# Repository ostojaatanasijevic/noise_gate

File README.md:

# TPI pedals - BMF

## Schematic

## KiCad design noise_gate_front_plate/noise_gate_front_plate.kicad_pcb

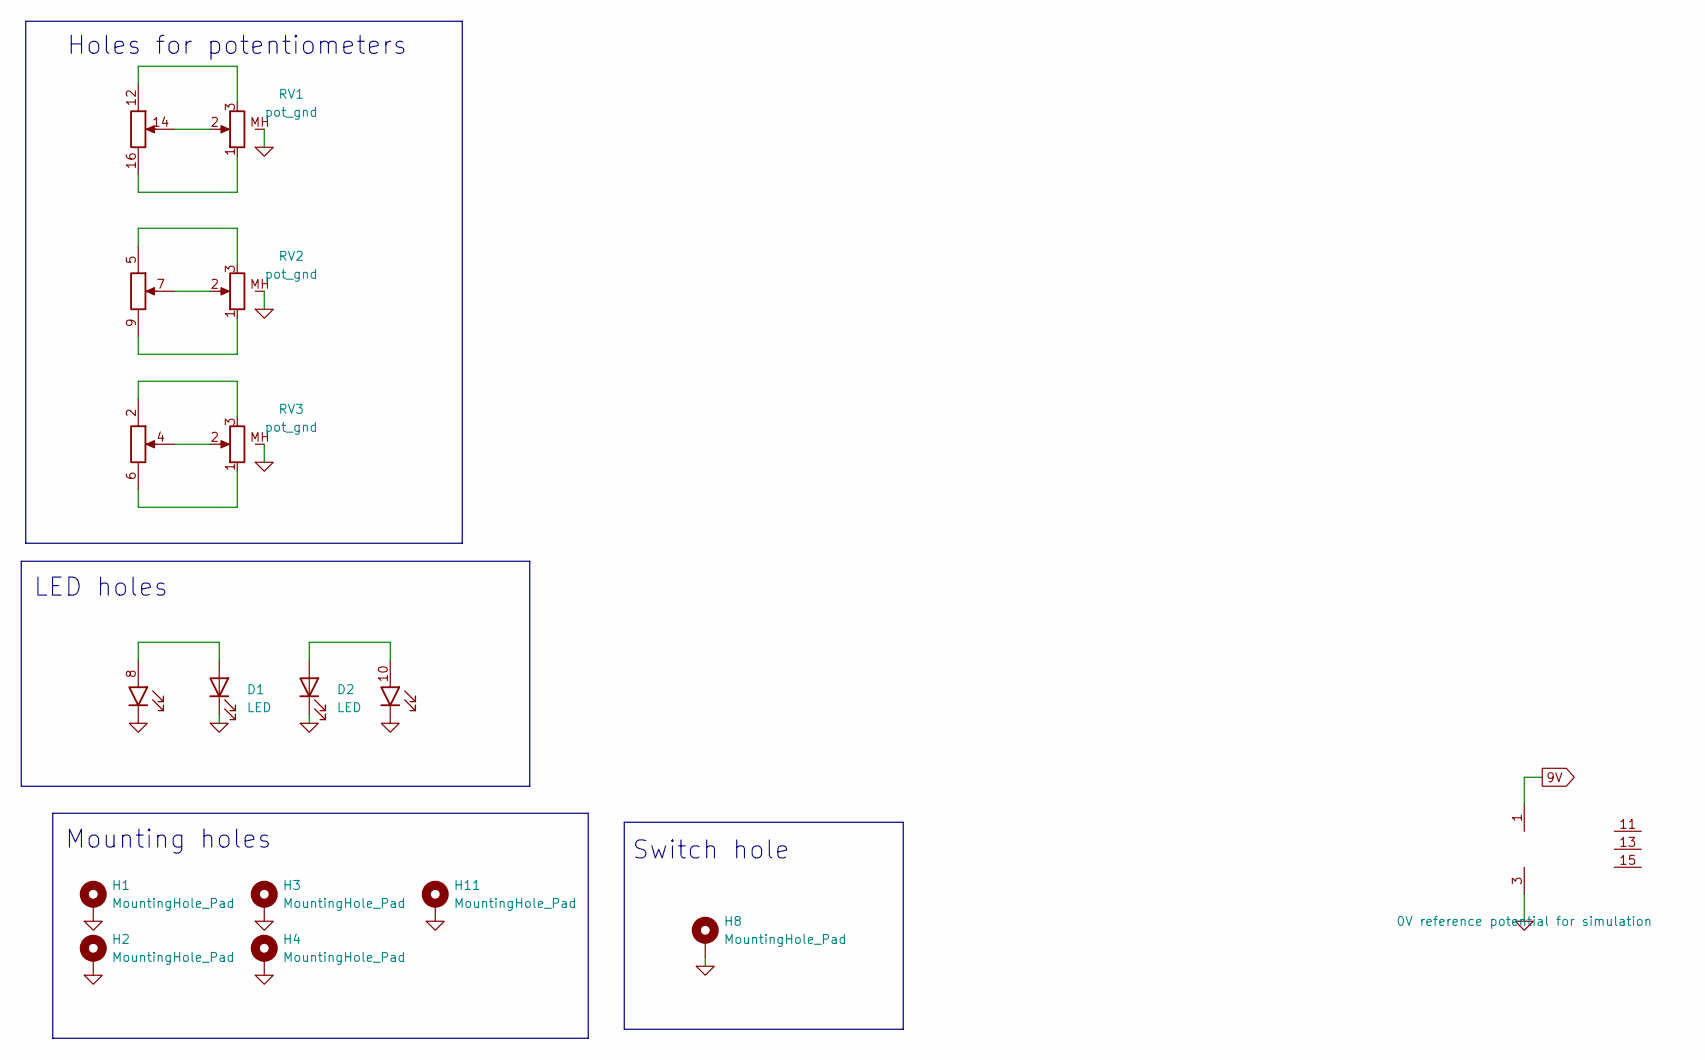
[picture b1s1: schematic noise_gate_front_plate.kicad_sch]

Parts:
D1: LED; red_led
D2: LED; green_led
H1, H2, H3, H4, H11: MountingHole_Pad; MountingHole_3.2mm_M3_DIN965_Pad_TopBottom
H8: MountingHole_Pad; plated_switch_hole
J1: top_panel_connector; IDC-Header_2x08_faux_SMD
RV1, RV2, RV3: pot_gnd; top_plate_pot

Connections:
0: D1.1 (K), D2.1 (K), H1.1, H2.1, H3.1, H4.1, H8.1, H11.1, J1.3 (GND), RV1.MH (2), RV2.MH (2), RV3.MH (2)
9V: J1.1 (VCC)
unnamed: D1.2 (A), J1.8
unnamed: D2.2 (A), J1.10
unnamed: J1.2, RV3.3
unnamed: J1.4, RV3.2
unnamed: J1.6, RV3.1
unnamed: J1.5, RV2.3
unnamed: J1.7, RV2.2
unnamed: J1.9, RV2.1
unnamed: J1.12, RV1.3
unnamed: J1.14, RV1.2
unnamed: J1.16, RV1.1

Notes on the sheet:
Mounting holes
Switch hole
LED holes
Holes for potentiometers

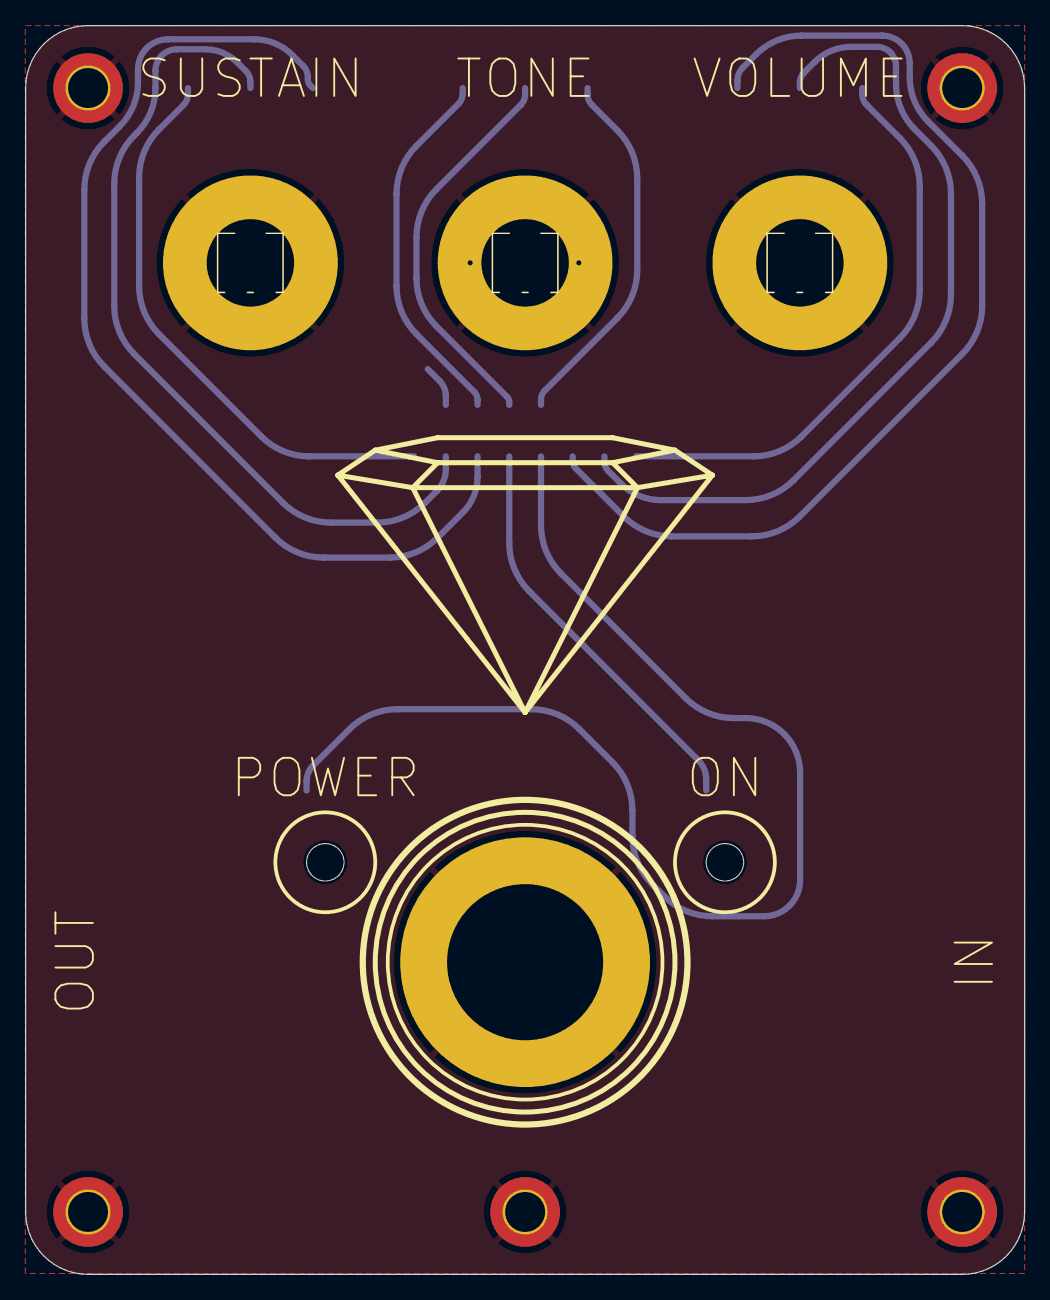
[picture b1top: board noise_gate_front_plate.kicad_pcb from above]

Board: 2 copper layers, 80.0 x 100.0 mm, 12 parts (1 on the bottom side), 12 nets.

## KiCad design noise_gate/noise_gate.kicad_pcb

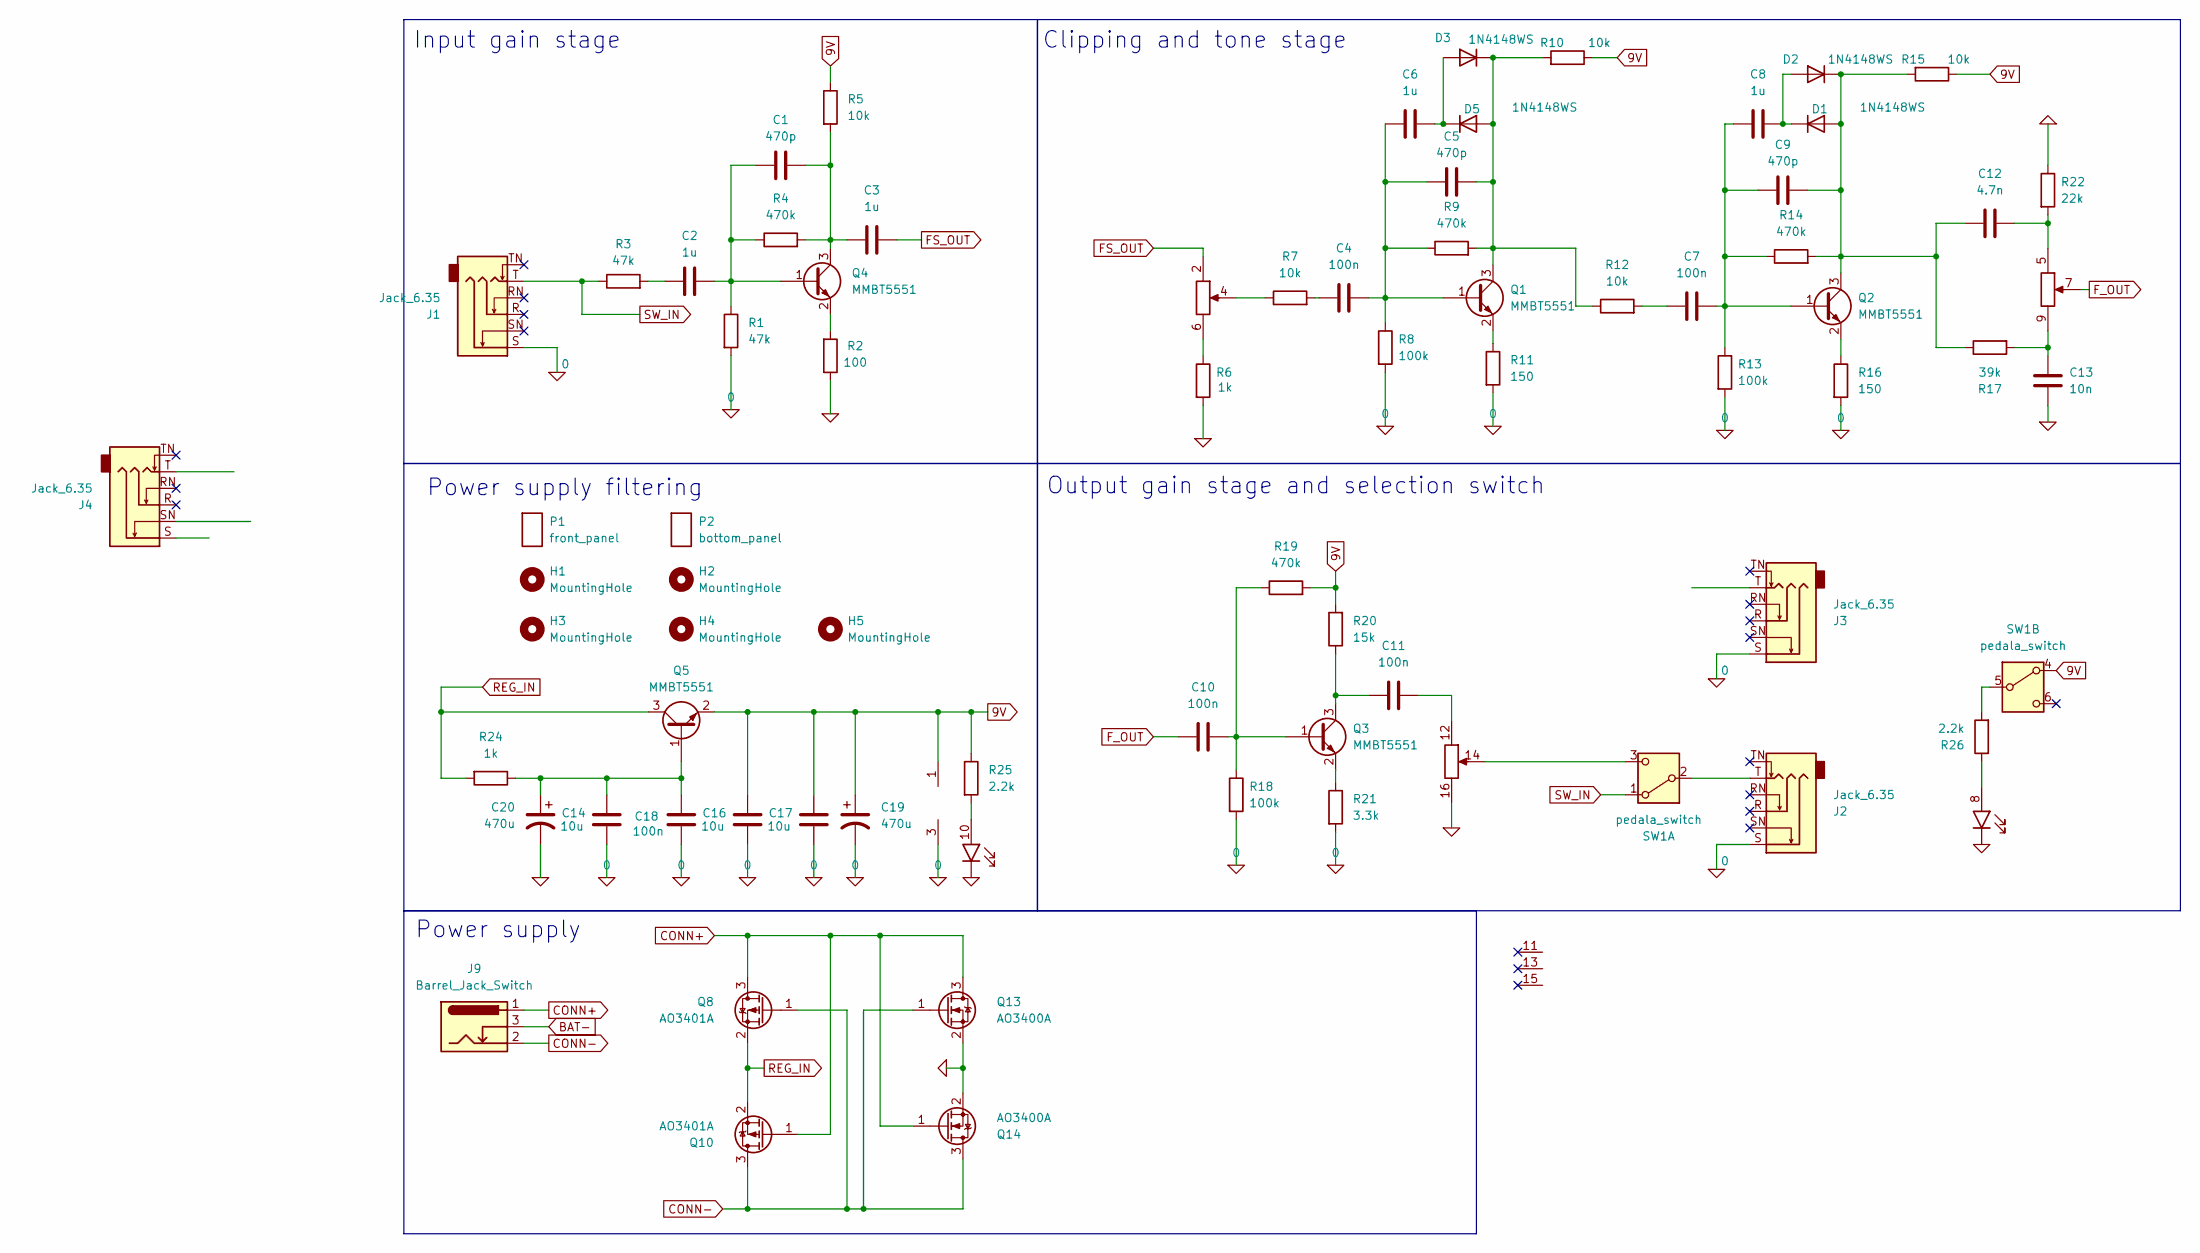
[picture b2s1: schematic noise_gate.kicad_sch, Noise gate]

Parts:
C1, C5, C9: 470p; C_0603_1608Metric_Pad1.08x0.95mm_HandSolder; LCSC C1620
C2, C3, C6, C8: 1u; C_0603_1608Metric_Pad1.08x0.95mm_HandSolder; LCSC C15849
C4, C7, C10, C11, C18: 100n; C_0603_1608Metric_Pad1.08x0.95mm_HandSolder; LCSC C14663
C12: 4.7n; C_0603_1608Metric_Pad1.08x0.95mm_HandSolder; LCSC C53987
C13: 10n; C_0603_1608Metric_Pad1.08x0.95mm_HandSolder; LCSC C57112
C14, C16, C17: 10u; C_0603_1608Metric_Pad1.08x0.95mm_HandSolder; LCSC C96446
C19, C20: 470u; CP_Radial_D8.0mm_P3.50mm
D1, D2, D3, D5: 1N4148WS; D_SOD-323; LCSC C2128
H1, H2, H3, H4, H5: MountingHole; M3_hole_with_spacer
J1, J2, J3, J4: Jack_6.35; Jack_6.35mm
J6: top_panel_connector; IDC-Header_2x08_P2.54mm_Vertical
J9: Barrel_Jack_Switch; BarrelJack
P1: front_panel; front_plate
P2: bottom_panel; bottom_plate
Q1, Q2, Q3, Q4, Q5: MMBT5551; SOT-23; LCSC C2145
Q8, Q10: AO3401A; SOT-23; LCSC C15127
Q13, Q14: AO3400A; SOT-23; LCSC C20917
R1, R3: 47k; R_0603_1608Metric_Pad0.98x0.95mm_HandSolder; LCSC C25819
R2: 100; R_0603_1608Metric_Pad0.98x0.95mm_HandSolder; LCSC C22775
R4, R9, R14, R19: 470k; R_0603_1608Metric_Pad0.98x0.95mm_HandSolder; LCSC C23178
R5, R7, R10, R12, R15: 10k; R_0603_1608Metric_Pad0.98x0.95mm_HandSolder; LCSC C25804
R6, R24: 1k; R_0603_1608Metric_Pad0.98x0.95mm_HandSolder; LCSC C21190
R8, R13, R18: 100k; R_0603_1608Metric_Pad0.98x0.95mm_HandSolder; LCSC C25803
R11, R16: 150; R_0603_1608Metric_Pad0.98x0.95mm_HandSolder; LCSC C22808
R17: 39k; R_0603_1608Metric_Pad0.98x0.95mm_HandSolder; LCSC C23153
R20: 15k; R_0603_1608Metric_Pad0.98x0.95mm_HandSolder; LCSC C22809
R21: 3.3k; R_0603_1608Metric_Pad0.98x0.95mm_HandSolder; LCSC C22978
R22: 22k; R_0603_1608Metric_Pad0.98x0.95mm_HandSolder; LCSC C31850
R25, R26: 2.2k; R_0603_1608Metric_Pad0.98x0.95mm_HandSolder; LCSC C4190
SW1: pedala_switch; foot_switch_tht_no_pad

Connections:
0: C13.1, C14.2, C16.2, C17.2, C18.1, C19.2, C20.2, J1.S, J2.S, J3.S, J6.3 (GND), J6.16, Q13.2 (S), Q14.2 (S), R1.2, R2.1, R6.2, R8.2, R11.2, R13.2, R16.2, R18.2, R21.2, R22.1
9V: C16.1, C17.1, C19.1, J6.1 (VCC), Q5.2 (E), R5.1, R10.1, R15.1, R19.2, R20.2, R25.1, SW1.4 (A)
BAT-: J9.3
CONN+: J9.1, Q8.3 (D), Q10.1 (G), Q13.3 (D), Q14.1 (G)
CONN-: J9.2, Q8.1 (G), Q10.3 (D), Q13.1 (G), Q14.3 (D)
FS_OUT: C3.2, J6.2
F_OUT: C10.1, J6.7
unnamed: C2.1, R3.2
unnamed: C4.1, R7.2
unnamed: C7.1, R12.2
unnamed: C9.2, C12.1, D1.2 (A), D2.1 (K), Q2.3 (C), R14.2, R15.2, R17.1
unnamed: C8.2, D1.1 (K), D2.2 (A)
unnamed: C6.2, D3.2 (A), D5.1 (K)
unnamed: C5.2, D3.1 (K), D5.2 (A), Q1.3 (C), R9.2, R10.2, R12.1
unnamed: J6.4, R7.1
unnamed: J6.6, R6.1
unnamed: C12.2, J6.5, R22.2
unnamed: C13.2, J6.9, R17.2
unnamed: C11.2, J6.12
unnamed: J6.14, SW1.3 (C)
unnamed: J6.8, R26.1
unnamed: J6.10, R25.2
unnamed: C4.2, C5.1, C6.1, Q1.1 (B), R8.1, R9.1
unnamed: Q1.2 (E), R11.1
unnamed: C7.2, C8.1, C9.1, Q2.1 (B), R13.1, R14.1
unnamed: Q2.2 (E), R16.1
unnamed: C10.2, Q3.1 (B), R18.1, R19.1
unnamed: C11.1, Q3.3 (C), R20.1
unnamed: Q3.2 (E), R21.1
unnamed: C1.1, C2.2, Q4.1 (B), R1.1, R4.1
unnamed: C1.2, C3.1, Q4.3 (C), R4.2, R5.2
unnamed: Q4.2 (E), R2.2
unnamed: C14.1, C18.2, C20.1, Q5.1 (B), R24.1
unnamed: J2.T, SW1.2 (B)
unnamed: R26.2, SW1.5 (B)
REG_IN: Q5.3 (C), Q8.2 (S), Q10.2 (S), R24.2
SW_IN: J1.T, R3.1, SW1.1 (A)

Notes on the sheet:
Power supply filtering
Input gain stage
Output gain stage and selection switch
Clipping and tone stage
Power supply

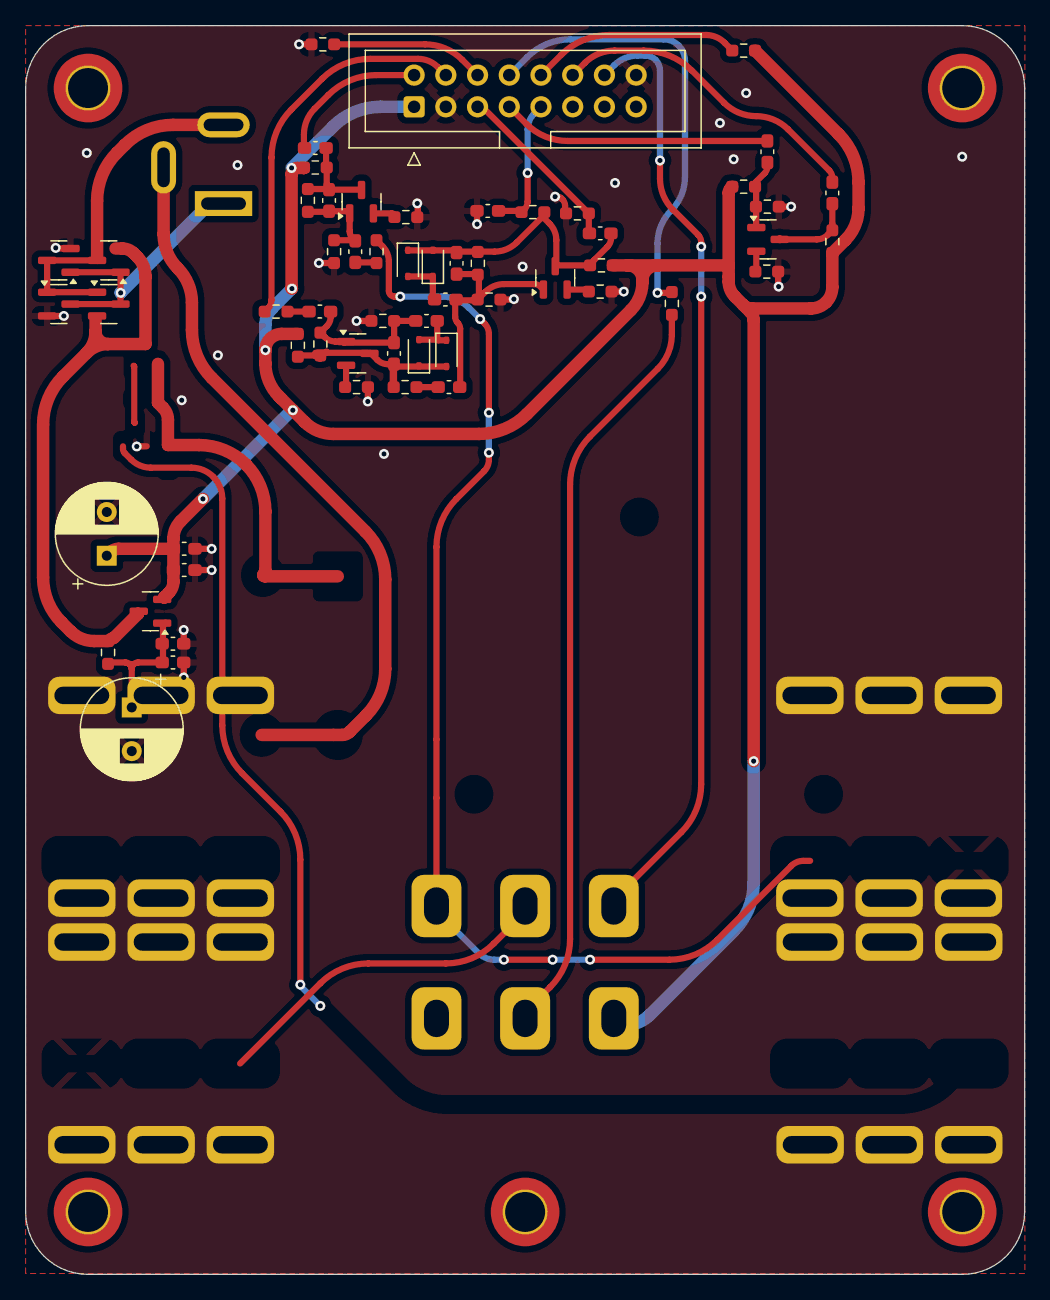
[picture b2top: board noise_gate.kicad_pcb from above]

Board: 2 copper layers, 80.0 x 100.0 mm, 71 parts (0 on the bottom side), 36 nets.

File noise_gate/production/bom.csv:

Designator,Footprint,Quantity,Value,LCSC Part #
"C1, C5, C9",0603,3,470p,C1620
"C10, C11, C18, C4, C7",0603,5,100n,C14663
C12,0603,1,4.7n,C53987
C13,0603,1,10n,C57112
"C14, C16, C17",0603,3,10u,C96446
"C2, C3, C6, C8",0603,4,1u,C15849
"D1, D2, D3, D5",D_SOD-323,4,1N4148WS,C2128
"Q1, Q2, Q3, Q4, Q5",SOT-23,5,MMBT5551,C2145
"Q10, Q6, Q8",SOT-23,3,AO3401A,C15127
"Q12, Q13, Q14",SOT-23,3,AO3400A,C20917
"R1, R3",0603,2,47k,C25819
"R10, R12, R15, R5, R7",0603,5,10k,C25804
"R11, R16",0603,2,150,C22808
"R13, R18, R23, R27, R8",0603,5,100k,C25803
"R14, R19, R4, R9",0603,4,470k,C23178
R17,0603,1,39k,C23153
R2,0603,1,100,C22775
R20,0603,1,15k,C22809
R21,0603,1,3.3k,C22978
R22,0603,1,22k,C31850
"R24, R6",0603,2,1k,C21190
"R25, R26",0603,2,2.2k,C4190

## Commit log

2025-05-28 Cloned the BMF, noise gate init.
2025-06-01 White pcbs.
2025-06-01 3d bodies.
